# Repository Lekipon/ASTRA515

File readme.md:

## *ASTRA 515 : A Symmetrical 5x15 Ortholinear Keyboard*

------

------

## **概要**

ASTRA 515は一体型の60％キーボードとほぼ同じサイズで5x15のオーソリニア（格子配列）となっている自作キーボードキットです。組立の難易度は決して高くないですが、キー数が多い故にハンダ付け箇所が多い点にご了承ください。

なお、ファームウェアは [QMK Firmware](https://github.com/qmk/qmk_firmware) を使用しています。

<br>

## 特徴

- ProMicro1個だけで可能な限り多くの実装をするためにDuplexMatrixの配線手法を利用。

- 左右の手のホームポジションの間隔を適度に離し、使用頻度の少ないキーを中央の区画に寄せた対称型オーソリニアレイアウト（全て1Uの構成にすれば片側寄せの非対称型のレイアウトも可能ですが...）。

- スイッチ付きロータリーエンコーダー（アルプスEC11/EC12互換）を2箇所に搭載可能。
- 好みに応じて親指周辺のキーを「1Ux3」または「1.5Ux2」の構成を選択可能（上の見本写真を参照）。また、中央下部のキーを縦の2U構成に変更することも可能（凸型配置の独立カーソルキーが不要な人向け、一般的には全て1Uの構成を推奨します）。

- RGBLED（WS2812B）による3連インジゲータの発光で「CapsLock」「NumLock」の状態を表示。また発光色によりレイヤーの状態を表示。

- RGBLEDのアンダーグロウに対応。なお、ハンダ付けの難易度がやや高いRGBLEDのみPCBに実装済。

- Kailhソケットにより大部分の区画がキースイッチの交換に対応（※中央下段の一部の区画を除く）。
- 標準添付のProMicroはUSBコネクタが「もげる」心配の無いMini-Bタイプを採用<br>（※別売となりますが普通のProMicroやElite-Cも使用出来ます）。

<br>

## キットに含まれている部品

1：PCB 1枚（RGBLEDを表面に3カ所、裏面に13カ所実装済）

2：スイッチマウントプレート

3：アクリルプレート3種（ボトムプレート用、トップカバー用、底上げ用、各1枚）

4：M2x8mmネジ（12本）

5：M2x5mmネジ（12本）

6：M2ワッシャー（8枚）

7：M2x12mmスタッドスペーサー（4本）

8：M2x4mmスペーサー（12本）

9：M2x3mmスペーサー（8本）

10：ゴム足（小3個、大3個）

11：Kailh PCBソケット（MX用・65個）

12：ダイオード（リードタイプ・75個）

13：ProMicro（Mini-Bタイプ・1個）および12ピンコンスルー（2本）

14：4ピンタクタイルスイッチ（リセットスイッチ用・1個）

<br>

## キットとは別に用意が必要な部品

- Cherry MX互換キースイッチ（73個）

- 1Uキーキャップ（73個）

- スイッチ付きロータリーエンコーダおよびツマミ（各2個）。なお、ロータリーエンコーダを使用しない場合はキースイッチと1Uキーキャップの必要数は各75個となります。

- USBケーブル（Mini-Bタイプ・1本）

<br>

## 必要な工具類

- ハンダごて（HAKKO FX600を推奨・別売コテ先はT18-C2かT18-D16がおすすめ）
- ハンダこて台
- 先が細いピンセット（ダイオードの足を曲げる際に必要）
- 普通のハンダ（スズ60％/鉛40％）およびハンダ吸い取り線
- フラックス（洗浄液もあるとなお良し）
- 精密ドライバーセット（100均のものでOK）
- マスキングテープ
- ニッパー
- プライヤー

<br>

## ビルドガイド

#### [**1：組立手順**](https://github.com/Lekipon/ASTRA515/blob/master/doc/buildguide.md)

#### [**2：デフォルトキーマップとQMKファームウェアについて**](https://github.com/Lekipon/ASTRA515/blob/master/doc/firmware.md)

#### [**3：ProMicroの換装について・他**](https://github.com/Lekipon/ASTRA515/blob/master/doc/promicro.md)

#### [**４：ロータリーエンコーダの選定について（沼）**](https://github.com/Lekipon/ASTRA515/blob/master/doc/re_numa.md)

<br>

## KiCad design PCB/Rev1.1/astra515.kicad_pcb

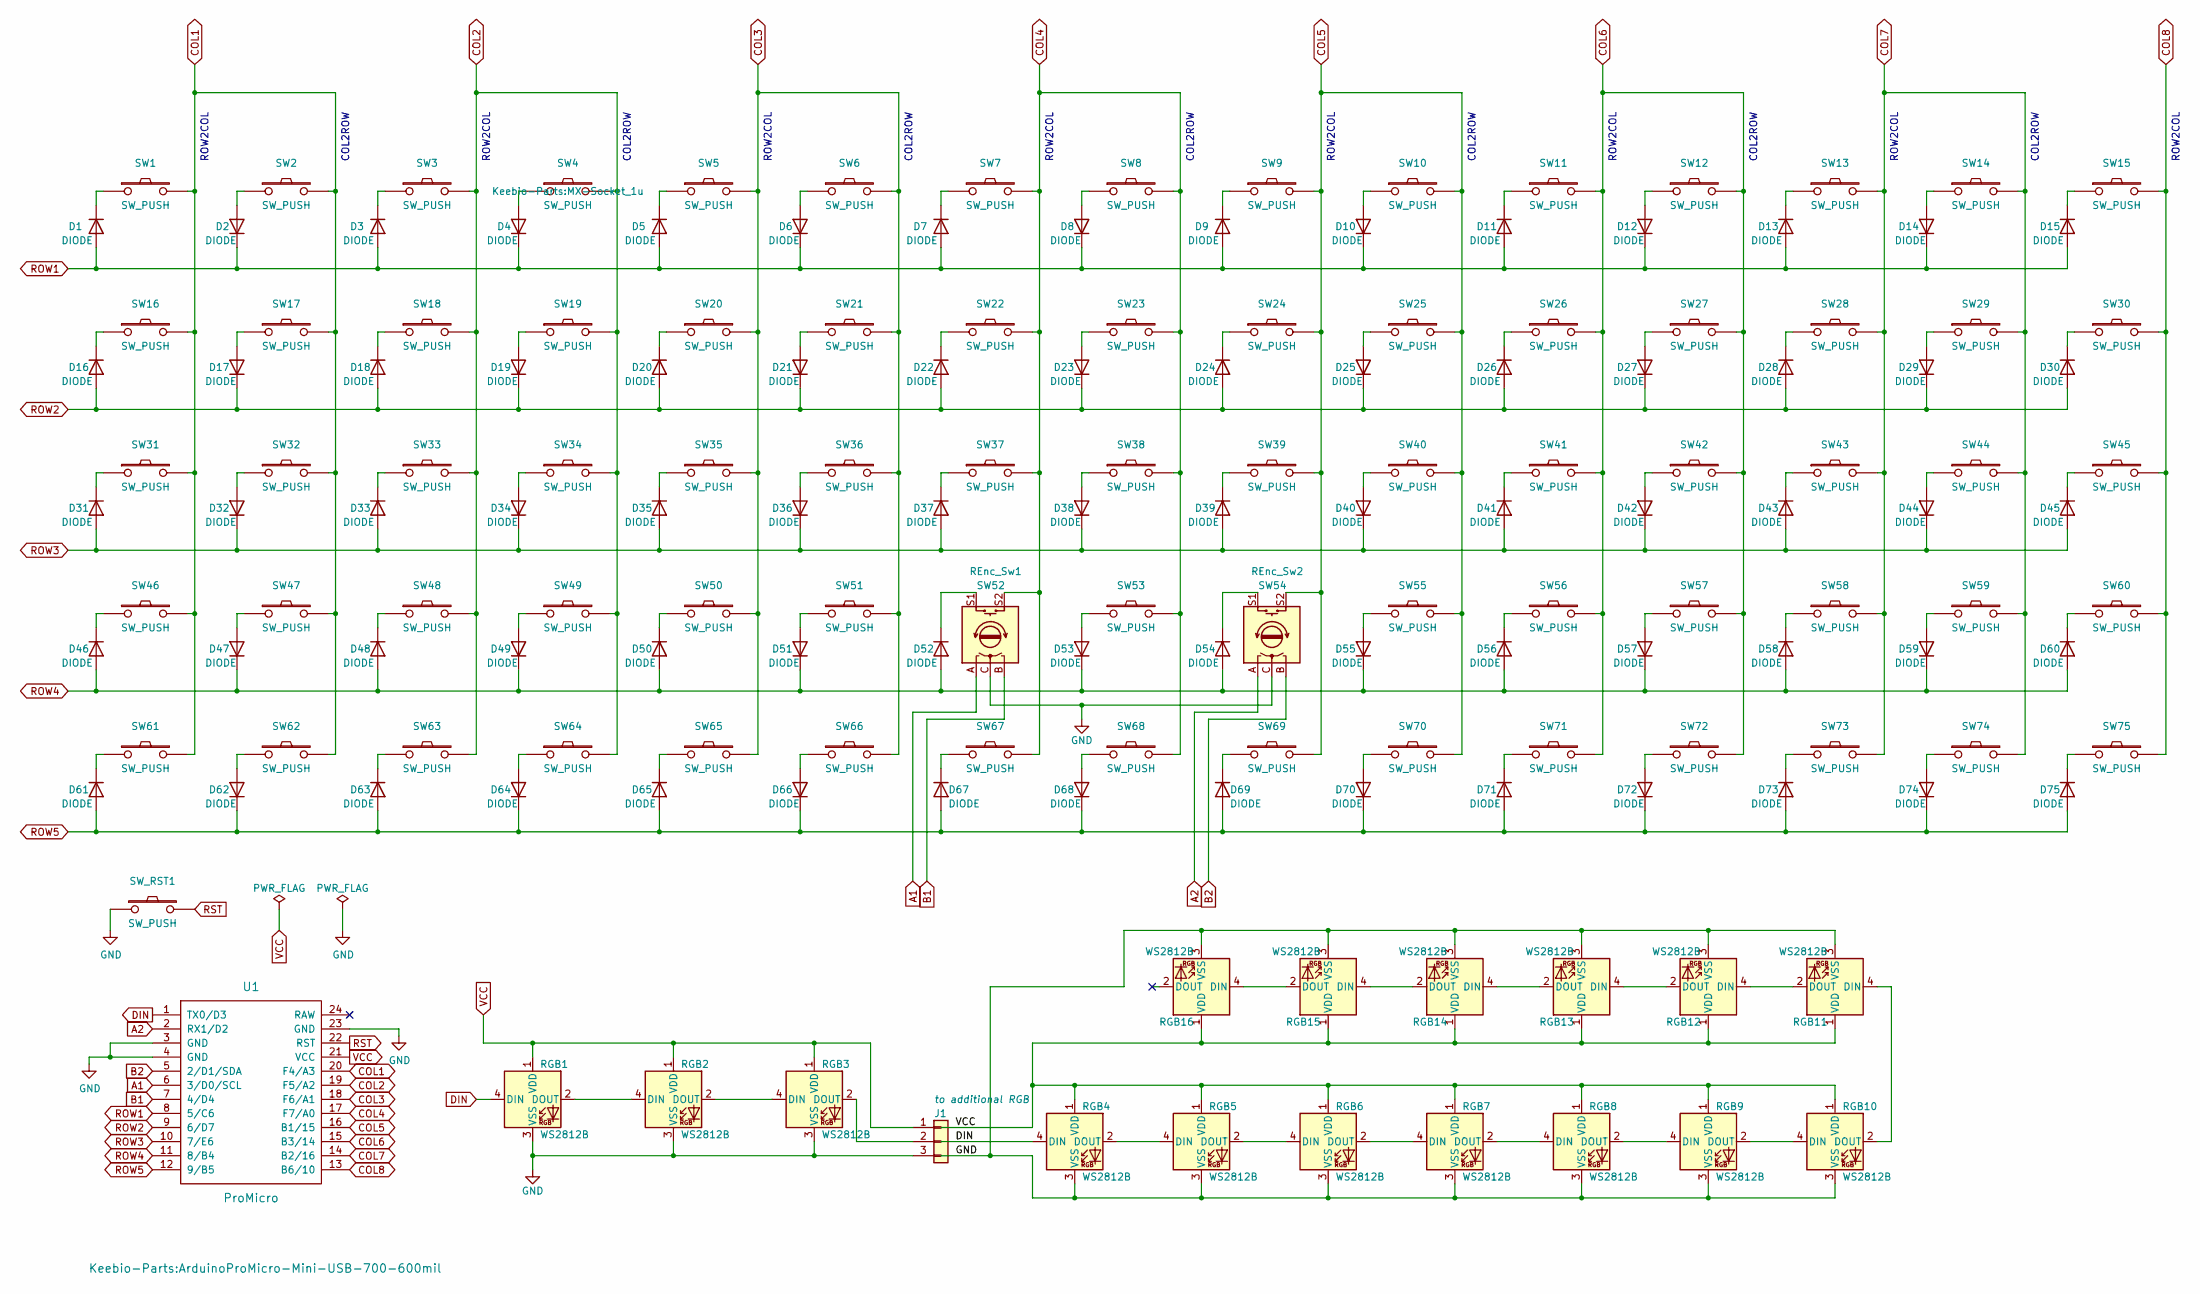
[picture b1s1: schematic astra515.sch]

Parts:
D1, D2, D3, D4, D5, D6, D7, D8, D9, D10, D11, D12, D13, D14, D15, D16, D17, D18, D19, D20, D21, D22, D23, D24, D25, D26, D27, D28, D29, D30, D31, D32, D33, D34, D35, D36, D37, D38, D39, D40, D41, D42, D43, D44, D45, D46, D47, D48, D49, D50, D51, D52, D53, D54, D55, D56, D57, D58, D59, D60, D61, D62, D63, D64, D65, D66, D67, D68, D69, D70, D71, D72, D73, D74, D75: DIODE; D3_TH_v2_6.35mm
J1: to additional RGB; PinHeader_1x03_P2.54mm_Vertical
RGB1, RGB2, RGB3, RGB4, RGB5, RGB6, RGB7, RGB8, RGB9, RGB10, RGB11, RGB12, RGB13, RGB14, RGB15, RGB16: WS2812B
SW1, SW2, SW3, SW4, SW5, SW6, SW7, SW8, SW9, SW10, SW11, SW12, SW13, SW14, SW15, SW16, SW17, SW18, SW19, SW20, SW21, SW22, SW23, SW24, SW25, SW26, SW27, SW28, SW29, SW30, SW31, SW32, SW33, SW34, SW35, SW36, SW37, SW38, SW39, SW40, SW41, SW42, SW43, SW44, SW45, SW46, SW47, SW48, SW49, SW50, SW51, SW55, SW56, SW57, SW58, SW59, SW60, SW61, SW62, SW63, SW64, SW72, SW73, SW74, SW75: SW_PUSH; MX-Socket_1u
SW52: REnc_Sw1; RotaryEncoder_Alps_EC11E(MX-Switch)
SW53: SW_PUSH; MX_2U-StabFlip
SW54: REnc_Sw2; RotaryEncoder_Alps_EC11E(MX-Switch)
SW65, SW69: SW_PUSH; MX_1U_1.5U(Left)
SW66, SW68, SW70: SW_PUSH; MX_1u
SW67, SW71: SW_PUSH; MX_1U_1.5U(Right)
SW_RST1: SW_PUSH; ResetSW_4P
U1: ProMicro; ArduinoProMicro-Mini-USB-700-600mil

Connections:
A1: SW52.A, U1.6 (3/D0/SCL)
A2: SW54.A, U1.2 (RX1/D2)
B1: SW52.B, U1.7 (4/D4)
B2: SW54.B, U1.5 (2/D1/SDA)
COL1: SW1.2, SW2.2, SW16.2, SW17.2, SW31.2, SW32.2, SW46.2, SW47.2, SW61.2, SW62.2, U1.20 (F4/A3)
COL2: SW3.2, SW4.2, SW18.2, SW19.2, SW33.2, SW34.2, SW48.2, SW49.2, SW63.2, SW64.2, U1.19 (F5/A2)
COL3: SW5.2, SW6.2, SW20.2, SW21.2, SW35.2, SW36.2, SW50.2, SW51.2, SW65.2, SW66.2, U1.18 (F6/A1)
COL4: SW7.2, SW8.2, SW22.2, SW23.2, SW37.2, SW38.2, SW52.S2, SW53.2, SW67.2, SW68.2, U1.17 (F7/A0)
COL5: SW9.2, SW10.2, SW24.2, SW25.2, SW39.2, SW40.2, SW54.S2, SW55.2, SW69.2, SW70.2, U1.16 (B1/15)
COL6: SW11.2, SW12.2, SW26.2, SW27.2, SW41.2, SW42.2, SW56.2, SW57.2, SW71.2, SW72.2, U1.15 (B3/14)
COL7: SW13.2, SW14.2, SW28.2, SW29.2, SW43.2, SW44.2, SW58.2, SW59.2, SW73.2, SW74.2, U1.14 (B2/16)
COL8: SW15.2, SW30.2, SW45.2, SW60.2, SW75.2, U1.13 (B6/10)
DIN: RGB1.4 (DIN), U1.1 (TX0/D3)
GND: J1.3, RGB1.3 (VSS), RGB2.3 (VSS), RGB3.3 (VSS), RGB4.3 (VSS), RGB5.3 (VSS), RGB6.3 (VSS), RGB7.3 (VSS), RGB8.3 (VSS), RGB9.3 (VSS), RGB10.3 (VSS), RGB11.3 (VSS), RGB12.3 (VSS), RGB13.3 (VSS), RGB14.3 (VSS), RGB15.3 (VSS), RGB16.3 (VSS), SW52.C, SW54.C, SW_RST1.1, U1.3 (GND), U1.4 (GND), U1.23 (GND)
unnamed: D1.2 (K), SW1.1
unnamed: D2.1 (A), SW2.1
unnamed: D3.2 (K), SW3.1
unnamed: D4.1 (A), SW4.1
unnamed: D5.2 (K), SW5.1
unnamed: D6.1 (A), SW6.1
unnamed: D7.2 (K), SW7.1
unnamed: D8.1 (A), SW8.1
unnamed: D9.2 (K), SW9.1
unnamed: D10.1 (A), SW10.1
unnamed: D11.2 (K), SW11.1
unnamed: D12.1 (A), SW12.1
unnamed: D13.2 (K), SW13.1
unnamed: D14.1 (A), SW14.1
unnamed: D15.2 (K), SW15.1
unnamed: D16.2 (K), SW16.1
unnamed: D17.1 (A), SW17.1
unnamed: D18.2 (K), SW18.1
unnamed: D19.1 (A), SW19.1
unnamed: D20.2 (K), SW20.1
unnamed: D21.1 (A), SW21.1
unnamed: D22.2 (K), SW22.1
unnamed: D23.1 (A), SW23.1
unnamed: D24.2 (K), SW24.1
unnamed: D25.1 (A), SW25.1
unnamed: D26.2 (K), SW26.1
unnamed: D27.1 (A), SW27.1
unnamed: D28.2 (K), SW28.1
unnamed: D29.1 (A), SW29.1
unnamed: D30.2 (K), SW30.1
unnamed: D31.2 (K), SW31.1
unnamed: D32.1 (A), SW32.1
unnamed: D33.2 (K), SW33.1
unnamed: D34.1 (A), SW34.1
unnamed: D35.2 (K), SW35.1
unnamed: D36.1 (A), SW36.1
unnamed: D37.2 (K), SW37.1
unnamed: D38.1 (A), SW38.1
unnamed: D39.2 (K), SW39.1
unnamed: D40.1 (A), SW40.1
unnamed: D41.2 (K), SW41.1
unnamed: D42.1 (A), SW42.1
unnamed: D43.2 (K), SW43.1
unnamed: D44.1 (A), SW44.1
unnamed: D45.2 (K), SW45.1
unnamed: D46.2 (K), SW46.1
unnamed: D47.1 (A), SW47.1
unnamed: D48.2 (K), SW48.1
unnamed: D49.1 (A), SW49.1
unnamed: D50.2 (K), SW50.1
unnamed: D51.1 (A), SW51.1
unnamed: D52.2 (K), SW52.S1
unnamed: D53.1 (A), SW53.1
unnamed: D54.2 (K), SW54.S1
unnamed: D55.1 (A), SW55.1
unnamed: D56.2 (K), SW56.1
unnamed: D57.1 (A), SW57.1
unnamed: D58.2 (K), SW58.1
unnamed: D59.1 (A), SW59.1
unnamed: D60.2 (K), SW60.1
unnamed: D61.2 (K), SW61.1
unnamed: D62.1 (A), SW62.1
unnamed: D63.2 (K), SW63.1
unnamed: D64.1 (A), SW64.1
unnamed: D65.2 (K), SW65.1
unnamed: D66.1 (A), SW66.1
unnamed: D67.2 (K), SW67.1
unnamed: D68.1 (A), SW68.1
unnamed: D69.2 (K), SW69.1
unnamed: D70.1 (A), SW70.1
unnamed: D71.2 (K), SW71.1
unnamed: D72.1 (A), SW72.1
unnamed: D73.2 (K), SW73.1
unnamed: D74.1 (A), SW74.1
unnamed: D75.2 (K), SW75.1
unnamed: RGB1.2 (DOUT), RGB2.4 (DIN)
unnamed: RGB2.2 (DOUT), RGB3.4 (DIN)
unnamed: RGB4.2 (DOUT), RGB5.4 (DIN)
unnamed: RGB5.2 (DOUT), RGB6.4 (DIN)
unnamed: RGB6.2 (DOUT), RGB7.4 (DIN)
unnamed: RGB7.2 (DOUT), RGB8.4 (DIN)
unnamed: RGB8.2 (DOUT), RGB9.4 (DIN)
unnamed: RGB10.2 (DOUT), RGB11.4 (DIN)
unnamed: RGB9.2 (DOUT), RGB10.4 (DIN)
unnamed: RGB11.2 (DOUT), RGB12.4 (DIN)
unnamed: RGB12.2 (DOUT), RGB13.4 (DIN)
unnamed: RGB13.2 (DOUT), RGB14.4 (DIN)
unnamed: RGB14.2 (DOUT), RGB15.4 (DIN)
unnamed: RGB15.2 (DOUT), RGB16.4 (DIN)
ROW1: D1.1 (A), D2.2 (K), D3.1 (A), D4.2 (K), D5.1 (A), D6.2 (K), D7.1 (A), D8.2 (K), D9.1 (A), D10.2 (K), D11.1 (A), D12.2 (K), D13.1 (A), D14.2 (K), D15.1 (A), U1.8 (5/C6)
ROW2: D16.1 (A), D17.2 (K), D18.1 (A), D19.2 (K), D20.1 (A), D21.2 (K), D22.1 (A), D23.2 (K), D24.1 (A), D25.2 (K), D26.1 (A), D27.2 (K), D28.1 (A), D29.2 (K), D30.1 (A), U1.9 (6/D7)
ROW3: D31.1 (A), D32.2 (K), D33.1 (A), D34.2 (K), D35.1 (A), D36.2 (K), D37.1 (A), D38.2 (K), D39.1 (A), D40.2 (K), D41.1 (A), D42.2 (K), D43.1 (A), D44.2 (K), D45.1 (A), U1.10 (7/E6)
ROW4: D46.1 (A), D47.2 (K), D48.1 (A), D49.2 (K), D50.1 (A), D51.2 (K), D52.1 (A), D53.2 (K), D54.1 (A), D55.2 (K), D56.1 (A), D57.2 (K), D58.1 (A), D59.2 (K), D60.1 (A), U1.11 (8/B4)
ROW5: D61.1 (A), D62.2 (K), D63.1 (A), D64.2 (K), D65.1 (A), D66.2 (K), D67.1 (A), D68.2 (K), D69.1 (A), D70.2 (K), D71.1 (A), D72.2 (K), D73.1 (A), D74.2 (K), D75.1 (A), U1.12 (9/B5)
RST: SW_RST1.2, U1.22 (RST)
VCC: J1.1, RGB1.1 (VDD), RGB2.1 (VDD), RGB3.1 (VDD), RGB4.1 (VDD), RGB5.1 (VDD), RGB6.1 (VDD), RGB7.1 (VDD), RGB8.1 (VDD), RGB9.1 (VDD), RGB10.1 (VDD), RGB11.1 (VDD), RGB12.1 (VDD), RGB13.1 (VDD), RGB14.1 (VDD), RGB15.1 (VDD), RGB16.1 (VDD), U1.21 (VCC)

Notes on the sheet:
ROW2COL
COL2ROW

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
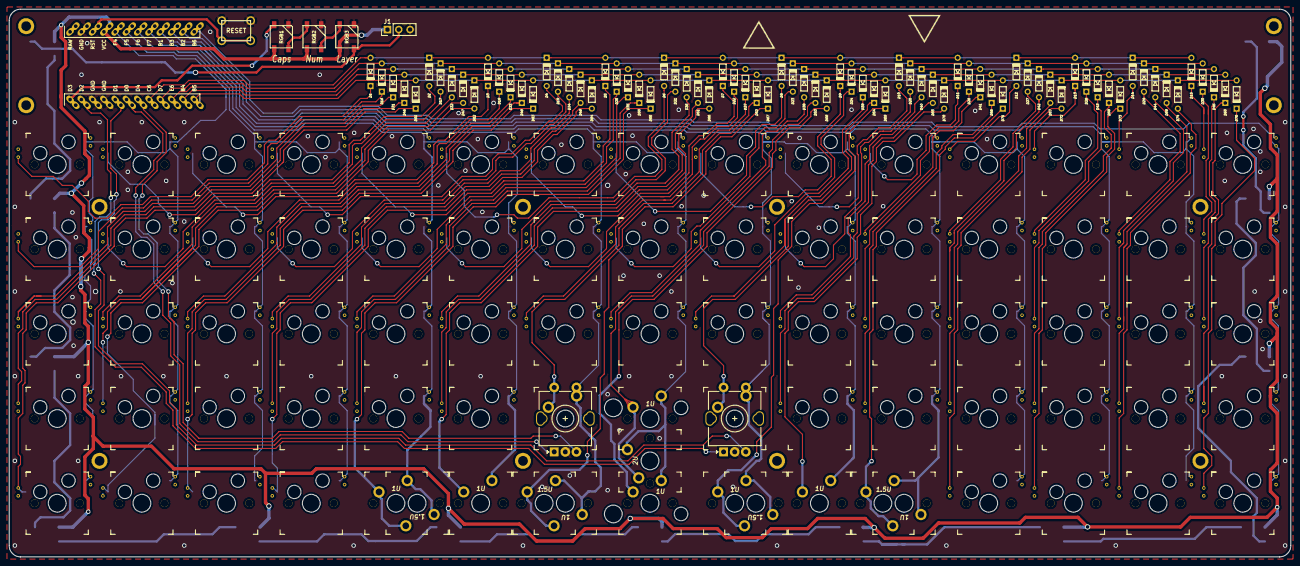
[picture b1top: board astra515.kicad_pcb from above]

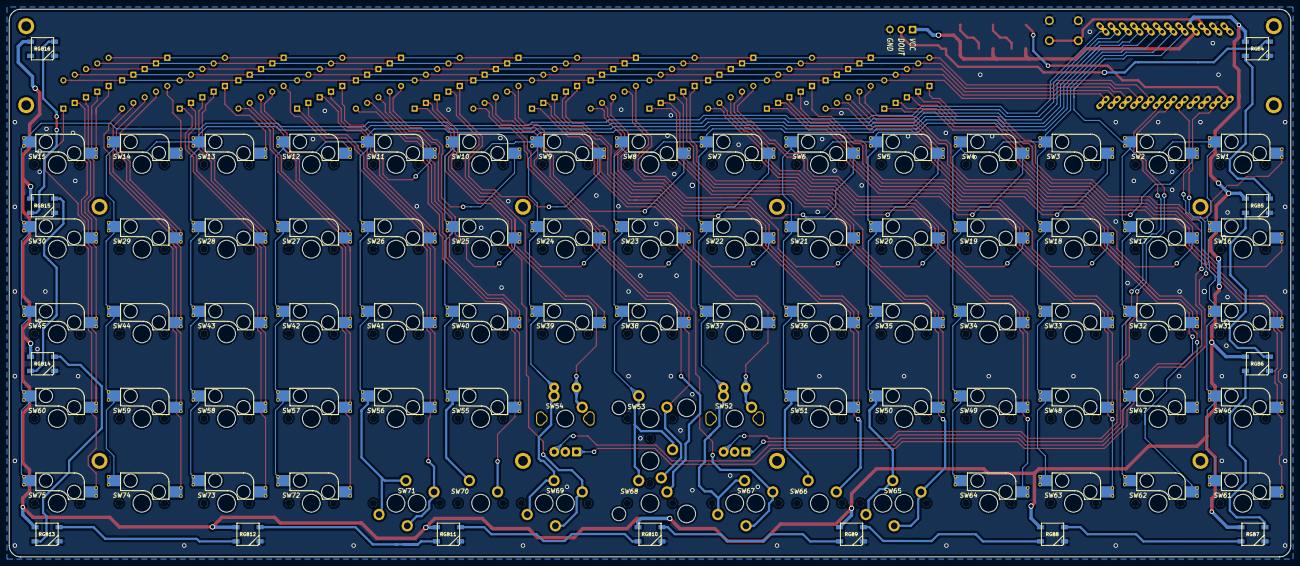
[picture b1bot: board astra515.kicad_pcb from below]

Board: 2 copper layers, 288.3 x 123.2 mm, 181 parts (13 on the bottom side), 111 nets.

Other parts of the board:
Ref**: Val**; M2_HOLE_3.6
Ref**#2, Ref**#3, Ref**#4, Ref**#5, Ref**#6, Ref**#7, Ref**#8, Ref**#9, Ref**#10, Ref**#11, Ref**#12: Val**; M2_HOLE_3.6

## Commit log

2020-11-14 Add PCB Data
2020-11-15 Add Images
2020-11-15 Removed kicad data
2020-11-16 Add image
2020-11-29 Update images
2021-04-11 Update hex files
2021-08-04 Update Hex
2021-08-05 Updete hex
2021-11-07 Add hex files
2022-08-28 add files
